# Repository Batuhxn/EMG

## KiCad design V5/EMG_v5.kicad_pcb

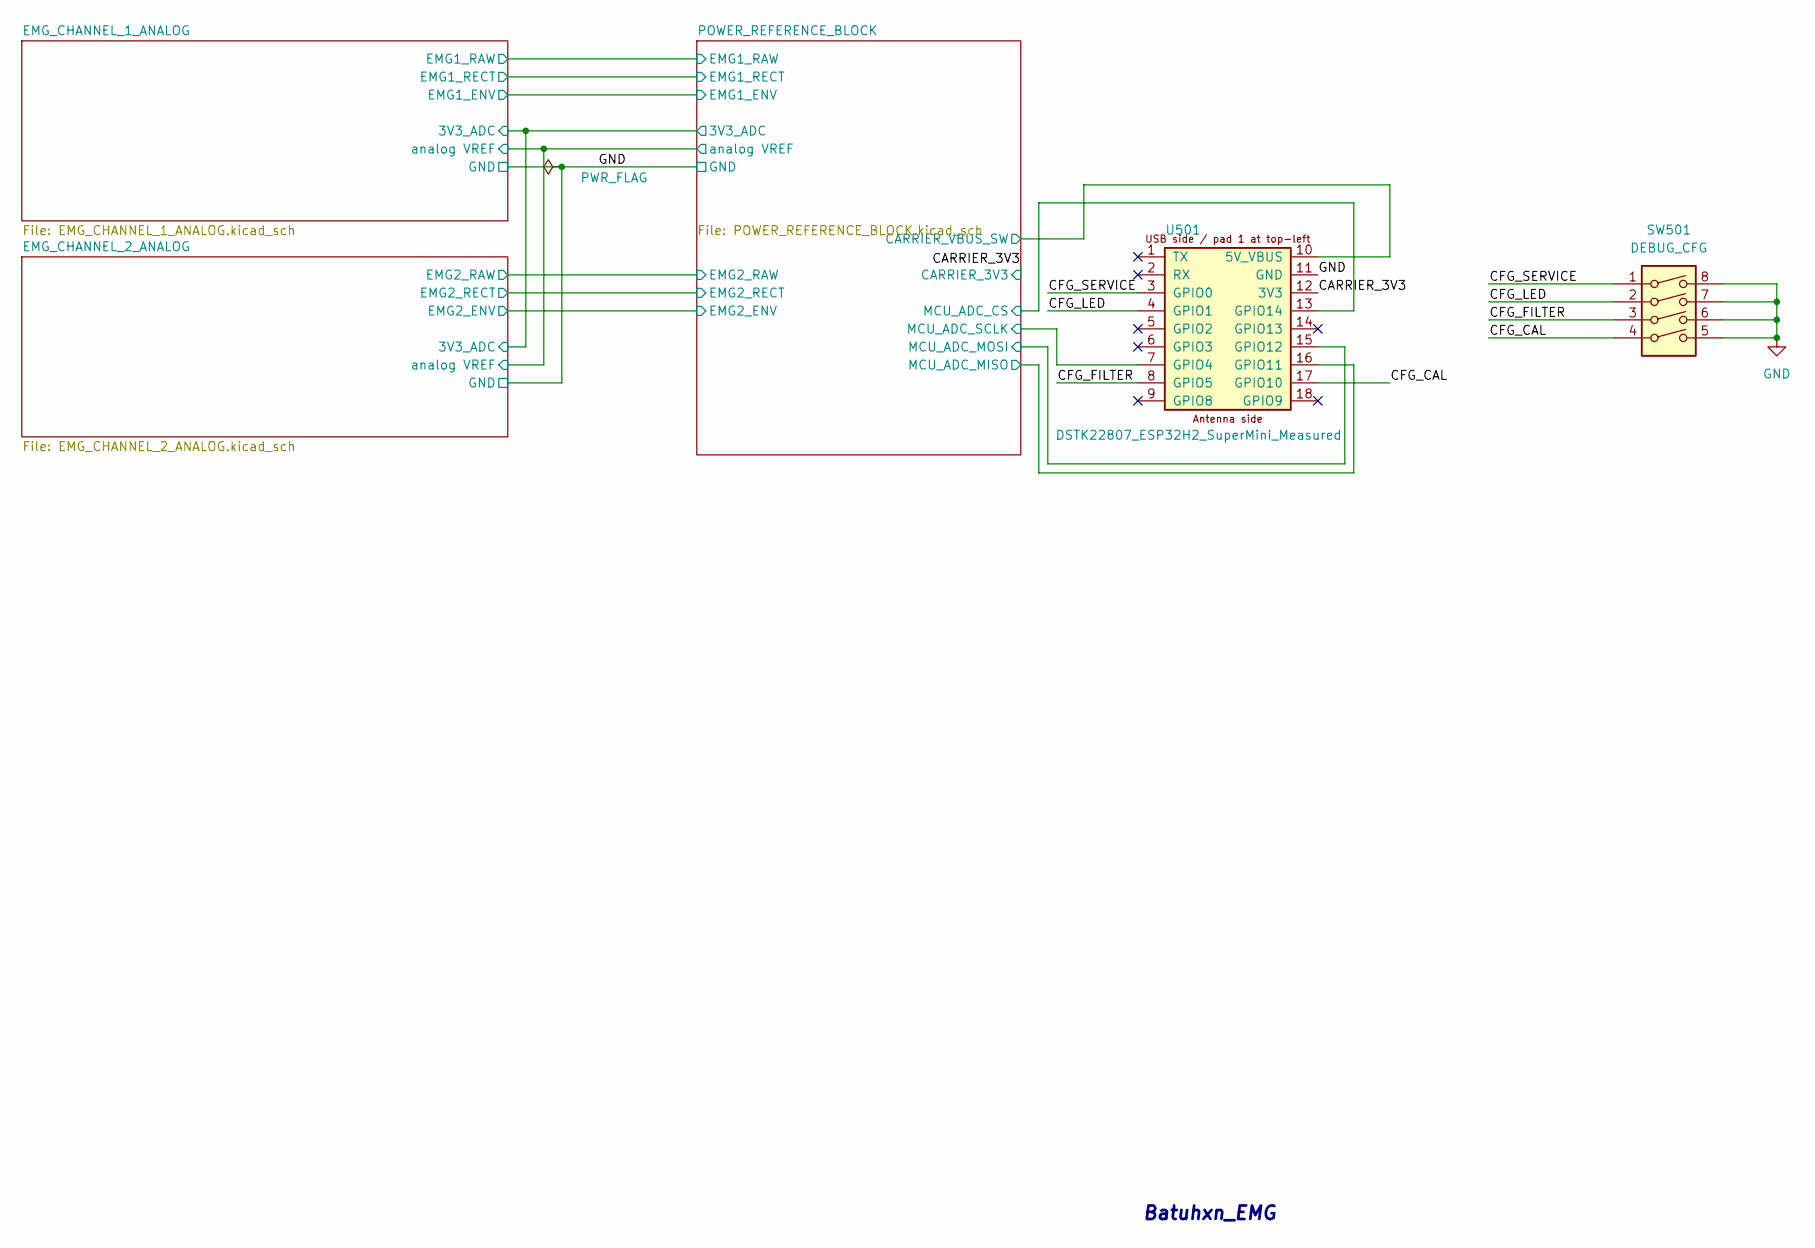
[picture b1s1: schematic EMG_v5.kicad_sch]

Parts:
SW501: DEBUG_CFG; SW_DIP_SPSTx04_Slide_9.78x12.34mm_W7.62mm_P2.54mm
U501: DSTK22807_ESP32H2_SuperMini_Measured; DSTK22807_ESP32H2_SuperMini_Carrier_Measured_THT

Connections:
/CARRIER_3V3: U501.12 (3V3); also elsewhere on the board
/CFG_CAL: SW501.4, U501.17 (GPIO10)
/CFG_FILTER: SW501.3, U501.8 (GPIO5)
/CFG_LED: SW501.2, U501.4 (GPIO1)
/CFG_SERVICE: SW501.1, U501.3 (GPIO0)
/POWER_REFERENCE_BLOCK/CARRIER_VBUS_SW: U501.10 (5V_VBUS); also elsewhere on the board
/POWER_REFERENCE_BLOCK/MCU_ADC_CS: U501.13 (GPIO14); also elsewhere on the board
/POWER_REFERENCE_BLOCK/MCU_ADC_MISO: U501.16 (GPIO11); also elsewhere on the board
/POWER_REFERENCE_BLOCK/MCU_ADC_MOSI: U501.15 (GPIO12); also elsewhere on the board
/POWER_REFERENCE_BLOCK/MCU_ADC_SCLK: U501.7 (GPIO4); also elsewhere on the board
GND: SW501.5, SW501.6, SW501.7, SW501.8, U501.11 (GND); also elsewhere on the board

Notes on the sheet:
Batuhxn_EMG

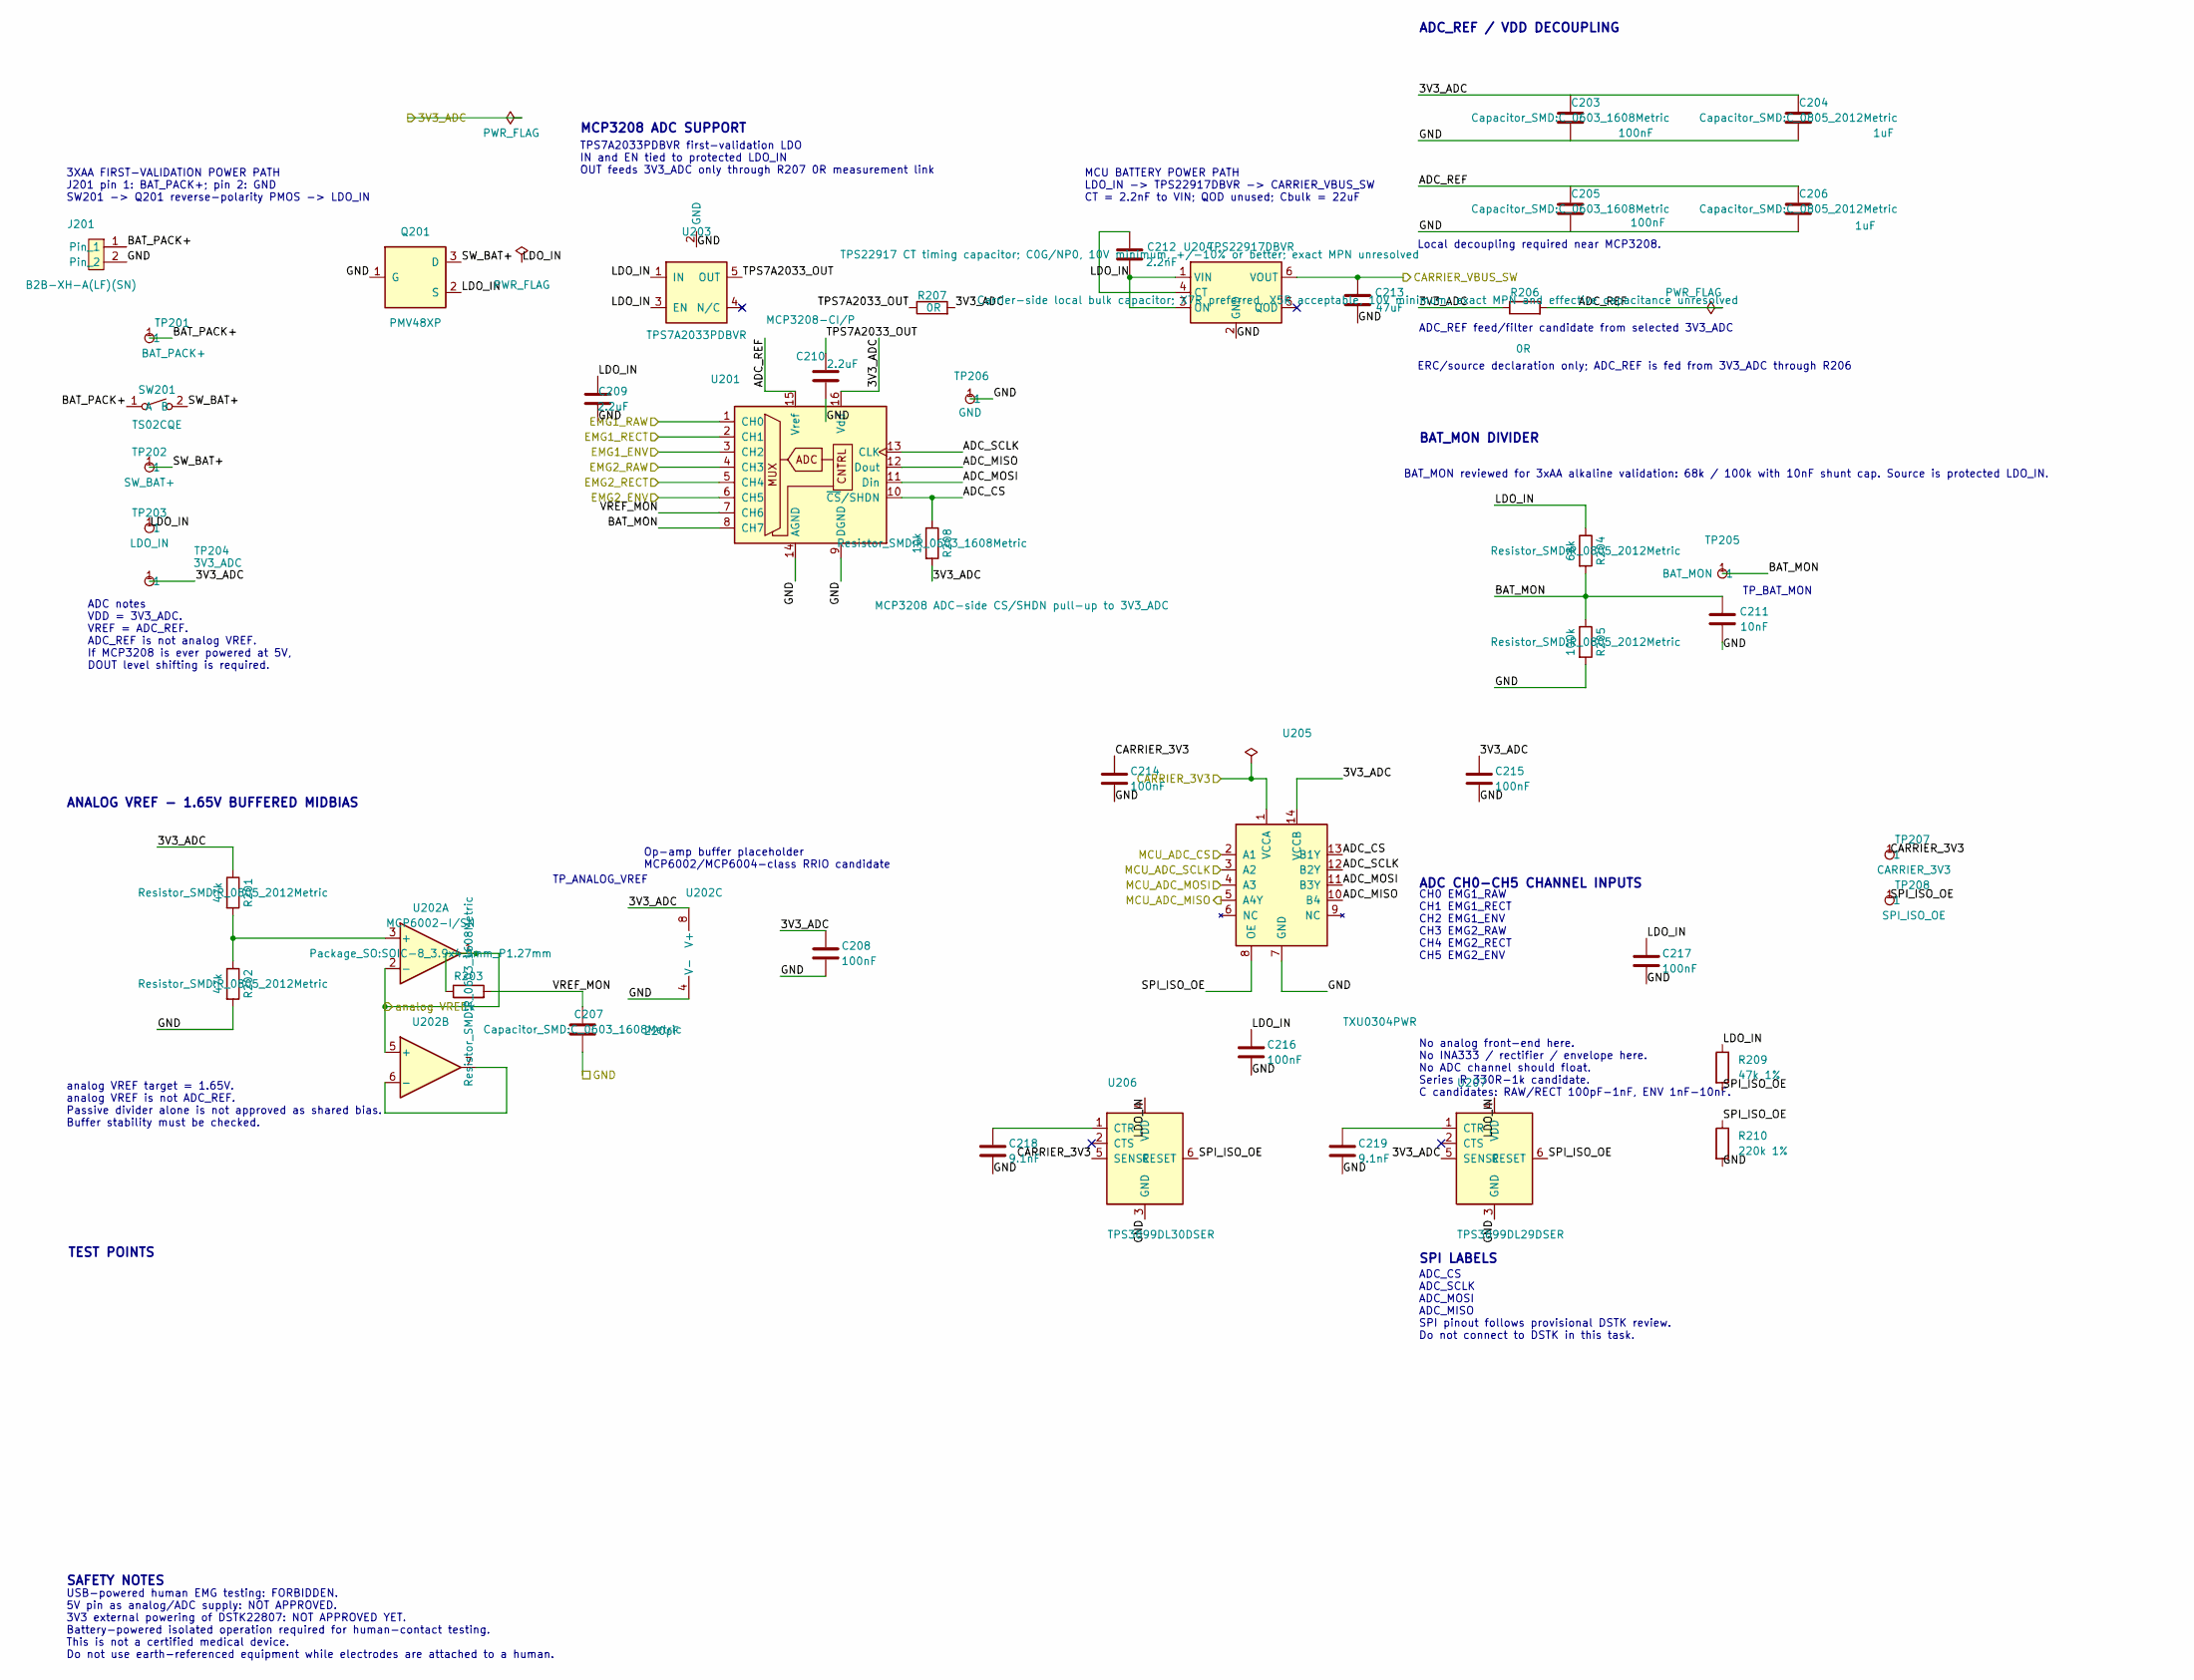
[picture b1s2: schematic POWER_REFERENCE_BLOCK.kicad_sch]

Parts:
C203, C205, C208, C214, C215, C216, C217: 100nF; C_0603_1608Metric
C204, C206: 1uF; C_0805_2012Metric
C207: 220pF; C_0603_1608Metric
C209, C210: 2.2uF; C_0805_2012Metric
C211: 10nF; C_0603_1608Metric
C212: 2.2nF; C_0603_1608Metric
C213: 47uF; C_1210_3225_Murata_GRM32_Reflow
C218, C219: 9.1nF; C_0603_1608Metric
J201: B2B-XH-A(LF)(SN); JST_XH_B2B-XH-A_1x02_P2.50mm_Vertical
Q201: PMV48XP; SOT-23
R201, R202: 47k; R_0805_2012Metric
R203: 1k; R_0603_1608Metric
R204: 68k; R_0805_2012Metric
R205: 100k; R_0805_2012Metric
R206, R207: 0R; R_0603_1608Metric
R208: 10k; R_0603_1608Metric
R209: 47k 1%; R_0603_1608Metric
R210: 220k 1%; R_0603_1608Metric
SW201: TS02CQE; TS02CQE_SPST_THT
TP201: BAT_PACK+; TestPoint_Pad_D1.0mm
TP202: SW_BAT+; TestPoint_Pad_D1.0mm
TP203: LDO_IN; TestPoint_Pad_D1.0mm
TP204: 3V3_ADC; TestPoint_Pad_D1.0mm
TP205: BAT_MON; TestPoint_Pad_D1.0mm
TP206: GND; TestPoint_Pad_D1.0mm
TP207: CARRIER_3V3; TestPoint_Pad_D1.0mm
TP208: SPI_ISO_OE; TestPoint_Pad_D1.0mm
U201: MCP3208-CI/P; DIP-16_W7.62mm
U202: MCP6002-I/SN; SOIC-8_3.9x4.9mm_P1.27mm
U203: TPS7A2033PDBVR; SOT-23-5
U204: TPS22917DBVR; SOT-23-6
U205: TXU0304PWR; TSSOP-14_4.4x5mm_P0.65mm
U206: TPS3899DL30DSER; WSON-6_1.5x1.5mm_P0.5mm
U207: TPS3899DL29DSER; WSON-6_1.5x1.5mm_P0.5mm

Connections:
/CARRIER_3V3: C214.1, TP207.1 (1_1), U205.1 (VCCA), U206.5 (SENSE); also elsewhere on the board
/EMG_CHANNEL_1_ANALOG/3V3_ADC: C203.1, C204.1, C208.1, C215.1, R201.1, R206.1, R207.2, R208.2, TP204.1 (1_1), U201.16 (Vdd), U202.8 (V+), U205.14 (VCCB), U207.5 (SENSE); also elsewhere on the board
/EMG_CHANNEL_1_ANALOG/EMG1_ENV: U201.3 (CH2); also elsewhere on the board
/EMG_CHANNEL_1_ANALOG/EMG1_RAW: U201.1 (CH0); also elsewhere on the board
/EMG_CHANNEL_1_ANALOG/EMG1_RECT: U201.2 (CH1); also elsewhere on the board
/EMG_CHANNEL_1_ANALOG/analog VREF: R203.1, U202.1, U202.2 (-), U202.5 (+); also elsewhere on the board
/EMG_CHANNEL_2_ANALOG/EMG2_ENV: U201.6 (CH5); also elsewhere on the board
/EMG_CHANNEL_2_ANALOG/EMG2_RAW: U201.4 (CH3); also elsewhere on the board
/EMG_CHANNEL_2_ANALOG/EMG2_RECT: U201.5 (CH4); also elsewhere on the board
/POWER_REFERENCE_BLOCK/ADC_CS: R208.1, U201.10 (~CS/SHDN), U205.13 (B1Y)
/POWER_REFERENCE_BLOCK/ADC_MISO: U201.12 (Dout), U205.10 (B4)
/POWER_REFERENCE_BLOCK/ADC_MOSI: U201.11 (Din), U205.11 (B3Y)
/POWER_REFERENCE_BLOCK/ADC_REF: C205.1, C206.1, R206.2, U201.15 (Vref)
/POWER_REFERENCE_BLOCK/ADC_SCLK: U201.13 (CLK), U205.12 (B2Y)
/POWER_REFERENCE_BLOCK/BAT_MON: C211.1, R204.2, R205.1, TP205.1 (1_1), U201.8 (CH7)
/POWER_REFERENCE_BLOCK/BAT_PACK+: J201.1, SW201.1 (A), TP201.1 (1_1)
/POWER_REFERENCE_BLOCK/CARRIER_VBUS_SW: C213.1, U204.6 (VOUT); also elsewhere on the board
/POWER_REFERENCE_BLOCK/LDO_IN: C209.1, C212.2, C216.1, C217.1, Q201.2 (S), R204.1, R209.1, TP203.1 (1_1), U203.1 (IN), U203.3 (EN), U204.1 (VIN), U204.3 (ON), U206.4 (VDD), U207.4 (VDD)
/POWER_REFERENCE_BLOCK/MCU_ADC_CS: U205.2 (A1); also elsewhere on the board
/POWER_REFERENCE_BLOCK/MCU_ADC_MISO: U205.5 (A4Y); also elsewhere on the board
/POWER_REFERENCE_BLOCK/MCU_ADC_MOSI: U205.4 (A3); also elsewhere on the board
/POWER_REFERENCE_BLOCK/MCU_ADC_SCLK: U205.3 (A2); also elsewhere on the board
/POWER_REFERENCE_BLOCK/SPI_ISO_OE: R209.2, R210.1, TP208.1 (1_1), U205.8 (OE), U206.6 (RESET), U207.6 (RESET)
/POWER_REFERENCE_BLOCK/SW_BAT+: Q201.3 (D), SW201.2 (B), TP202.1 (1_1)
/POWER_REFERENCE_BLOCK/TPS7A2033_OUT: C210.1, R207.1, U203.5 (OUT)
/POWER_REFERENCE_BLOCK/VREF_MON: C207.1, R203.2, U201.7 (CH6)
GND: C203.2, C204.2, C205.2, C206.2, C207.2, C208.2, C209.2, C210.2, C211.2, C213.2, C214.2, C215.2, C216.2, C217.2, C218.2, C219.2, J201.2, Q201.1 (G), R202.2, R205.2, R210.2, TP206.1 (1_1), U201.9 (DGND), U201.14 (AGND), U202.4 (V-), U203.2 (GND), U204.2 (GND), U205.7 (GND), U206.3 (GND), U207.3 (GND); also elsewhere on the board
unnamed: R201.2, R202.1, U202.3 (+)
unnamed: U202.6 (-), U202.7
unnamed: C212.1, U204.4 (CT)
unnamed: C218.1, U206.1 (CTR)
unnamed: C219.1, U207.1 (CTR)

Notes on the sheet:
MCP3208 ADC SUPPORT
ADC notes VDD = 3V3_ADC. VREF = ADC_REF. ADC_REF is not analog VREF. If MCP3208 is ever powered at 5V, DOUT level shifting is required.
ADC_REF / VDD DECOUPLING
Local decoupling required near MCP3208.
ANALOG VREF - 1.65V BUFFERED MIDBIAS
analog VREF target = 1.65V. analog VREF is not ADC_REF. Passive divider alone is not approved as shared bias. Buffer stability must be checked.
TP_ANALOG_VREF
Op-amp buffer placeholder MCP6002/MCP6004-class RRIO candidate
BAT_MON DIVIDER
TP_BAT_MON
ADC CH0-CH5 CHANNEL INPUTS
CH0 EMG1_RAW CH1 EMG1_RECT CH2 EMG1_ENV CH3 EMG2_RAW CH4 EMG2_RECT CH5 EMG2_ENV
No analog front-end here. No INA333 / rectifier / envelope here. No ADC channel should float. Series R 330R-1k candidate. C candidates: RAW/RECT 100pF-1nF, ENV 1nF-10nF.
SPI LABELS
ADC_CS ADC_SCLK ADC_MOSI ADC_MISO SPI pinout follows provisional DSTK review. Do not connect to DSTK in this task.
TEST POINTS
SAFETY NOTES
USB-powered human EMG testing: FORBIDDEN. 5V pin as analog/ADC supply: NOT APPROVED. 3V3 external powering of DSTK22807: NOT APPROVED YET. Battery-powered isolated operation required for human-contact testing. This is not a certified medical device. Do not use earth-referenced equipment while elect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
ADC_REF feed/filter candidate from selected 3V3_ADC
ERC/source declaration only; ADC_REF is fed from 3V3_ADC through R206
3XAA FIRST-VALIDATION POWER PATH J201 pin 1: BAT_PACK+; pin 2: GND SW201 -> Q201 reverse-polarity PMOS -> LDO_IN
TPS7A2033PDBVR first-validation LDO IN and EN tied to protected LDO_IN OUT feeds 3V3_ADC only through R207 0R measurement link
BAT_MON reviewed for 3xAA alkaline validation: 68k / 100k with 10nF shunt cap. Source is protected LDO_IN.
MCU BATTERY POWER PATH LDO_IN -> TPS22917DBVR -> CARRIER_VBUS_SW CT = 2.2nF to VIN; QOD unused; Cbulk = 22uF

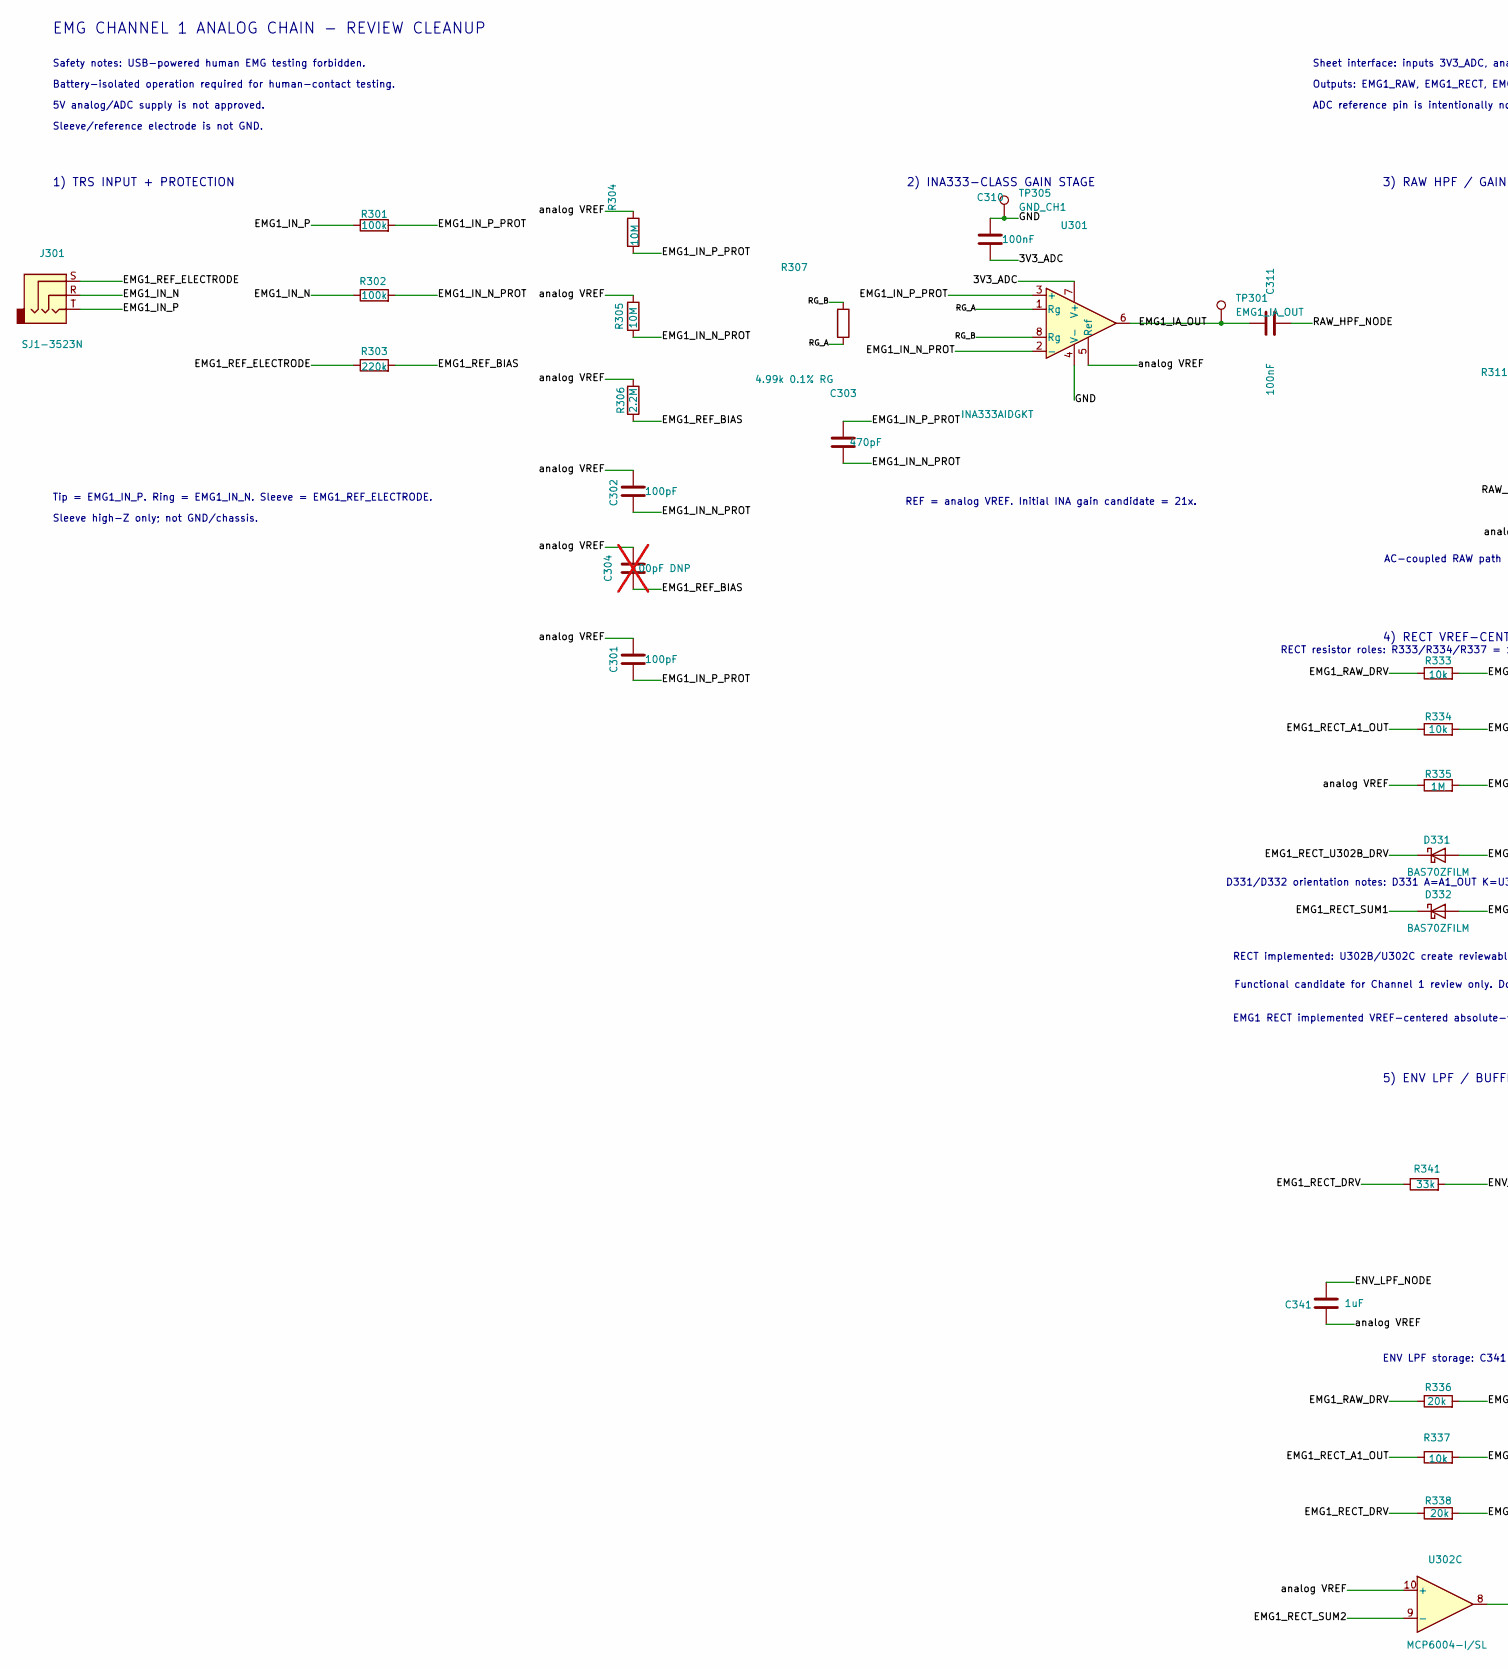
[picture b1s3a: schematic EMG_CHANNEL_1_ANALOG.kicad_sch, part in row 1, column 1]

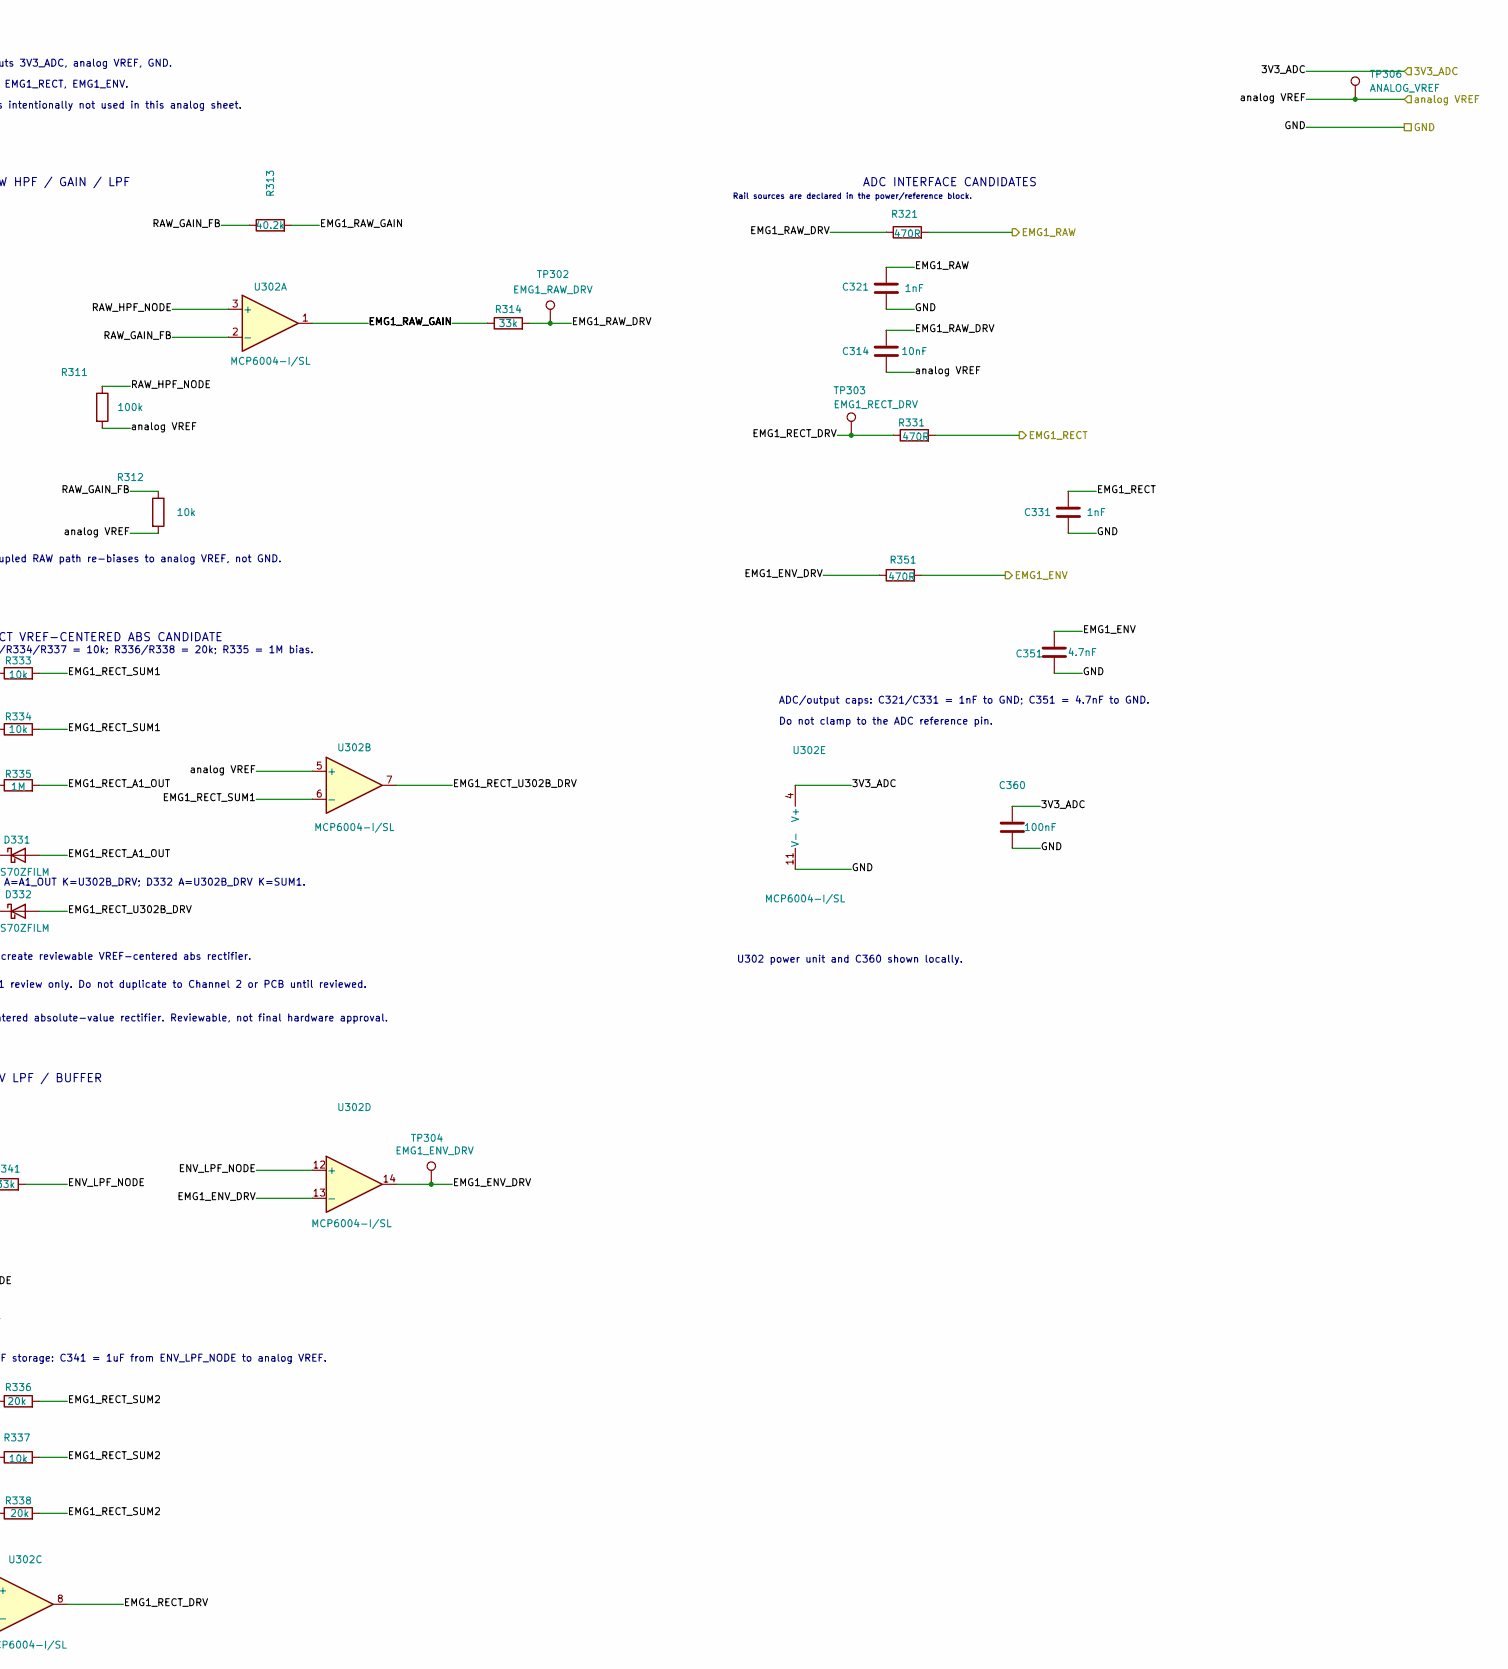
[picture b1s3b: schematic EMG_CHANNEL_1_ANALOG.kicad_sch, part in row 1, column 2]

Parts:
C301, C302: 100pF; C_0603_1608Metric
C303: 470pF; C_0603_1608Metric
C304: 100pF DNP; C_0603_1608Metric; not fitted
C310, C311: 100nF; C_0603_1608Metric
C314: 10nF; C_0603_1608Metric
C321, C331: 1nF; C_0805_2012Metric
C341: 1uF; C_0805_2012Metric
C351: 4.7nF; C_0805_2012Metric
C360: 100nF; C_0805_2012Metric
D331, D332: BAS70ZFILM; D_SOD-123
J301: SJ1-3523N; Jack_3.5mm_CUI_SJ1-3523N_Horizontal
R301, R302: 100k; R_1206_3216Metric
R303: 220k; R_1206_3216Metric
R304, R305: 10M; R_1206_3216Metric
R306: 2.2M; R_1206_3216Metric
R307: 4.99k 0.1% RG; R_0805_2012Metric
R311: 100k; R_0805_2012Metric
R312, R333, R334, R337: 10k; R_0805_2012Metric
R313: 40.2k; R_0805_2012Metric
R314, R341: 33k; R_0805_2012Metric
R321, R331, R351: 470R; R_0805_2012Metric
R335: 1M; R_0805_2012Metric
R336, R338: 20k; R_0805_2012Metric
TP301: EMG1_IA_OUT; TestPoint_Pad_D1.5mm
TP302: EMG1_RAW_DRV; TestPoint_Pad_D1.5mm
TP303: EMG1_RECT_DRV; TestPoint_Pad_D1.5mm
TP304: EMG1_ENV_DRV; TestPoint_Pad_D1.5mm
TP305: GND_CH1; TestPoint_Pad_D2.0mm
TP306: ANALOG_VREF; TestPoint_Pad_D1.5mm
U301: INA333AIDGKT; INA333_DGK_VSSOP-8_TI
U302: MCP6004-I/SL; SOIC-14_3.9x8.7mm_P1.27mm

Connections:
/EMG_CHANNEL_1_ANALOG/3V3_ADC: C310.2, C360.1, U301.7 (V+), U302.4 (V+); also elsewhere on the board
/EMG_CHANNEL_1_ANALOG/EMG1_ENV: C351.1, R351.2; also elsewhere on the board
/EMG_CHANNEL_1_ANALOG/EMG1_ENV_DRV: R351.1, TP304.1 (1_1), U302.13 (-), U302.14
/EMG_CHANNEL_1_ANALOG/EMG1_IA_OUT: C311.1, TP301.1 (1_1), U301.6
/EMG_CHANNEL_1_ANALOG/EMG1_IN_N: J301.R, R302.1
/EMG_CHANNEL_1_ANALOG/EMG1_IN_N_PROT: C302.2, C303.2, R302.2, R305.2, U301.2 (-)
/EMG_CHANNEL_1_ANALOG/EMG1_IN_P: J301.T, R301.1
/EMG_CHANNEL_1_ANALOG/EMG1_IN_P_PROT: C301.2, C303.1, R301.2, R304.2, U301.3 (+)
/EMG_CHANNEL_1_ANALOG/EMG1_RAW: C321.1, R321.2; also elsewhere on the board
/EMG_CHANNEL_1_ANALOG/EMG1_RAW_DRV: C314.1, R314.2, R321.1, R333.1, R336.1, TP302.1 (1_1)
/EMG_CHANNEL_1_ANALOG/EMG1_RAW_GAIN: R313.2, R314.1, U302.1
/EMG_CHANNEL_1_ANALOG/EMG1_RECT: C331.1, R331.2; also elsewhere on the board
/EMG_CHANNEL_1_ANALOG/EMG1_RECT_A1_OUT: D331.2 (A), R334.1, R335.2, R337.1
/EMG_CHANNEL_1_ANALOG/EMG1_RECT_DRV: R331.1, R338.1, R341.1, TP303.1 (1_1), U302.8
/EMG_CHANNEL_1_ANALOG/EMG1_RECT_SUM1: D332.1 (K), R333.2, R334.2, U302.6 (-)
/EMG_CHANNEL_1_ANALOG/EMG1_RECT_SUM2: R336.2, R337.2, R338.2, U302.9 (-)
/EMG_CHANNEL_1_ANALOG/EMG1_RECT_U302B_DRV: D331.1 (K), D332.2 (A), U302.7
/EMG_CHANNEL_1_ANALOG/EMG1_REF_BIAS: C304.2, R303.2, R306.2
/EMG_CHANNEL_1_ANALOG/EMG1_REF_ELECTRODE: J301.S, R303.1
/EMG_CHANNEL_1_ANALOG/ENV_LPF_NODE: C341.1, R341.2, U302.12 (+)
/EMG_CHANNEL_1_ANALOG/RAW_GAIN_FB: R312.1, R313.1, U302.2 (-)
/EMG_CHANNEL_1_ANALOG/RAW_HPF_NODE: C311.2, R311.1, U302.3 (+)
/EMG_CHANNEL_1_ANALOG/RG_A: R307.2, U301.1 (Rg)
/EMG_CHANNEL_1_ANALOG/RG_B: R307.1, U301.8 (Rg)
/EMG_CHANNEL_1_ANALOG/analog VREF: C301.1, C302.1, C304.1, C314.2, C341.2, R304.1, R305.1, R306.1, R311.2, R312.2, R335.1, TP306.1 (1_1), U301.5 (Ref), U302.5 (+), U302.10 (+); also elsewhere on the board
GND: C310.1, C321.2, C331.2, C351.2, C360.2, TP305.1 (1_1), U301.4 (V-), U302.11 (V-); also elsewhere on the board

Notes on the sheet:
EMG CHANNEL 1 ANALOG CHAIN - REVIEW CLEANUP
Safety notes: USB-powered human EMG testing forbidden.
Battery-isolated operation required for human-contact testing.
5V analog/ADC supply is not approved.
Sleeve/reference electrode is not GND.
Sheet interface: inputs 3V3_ADC, analog VREF, GND.
Outputs: EMG1_RAW, EMG1_RECT, EMG1_ENV.
ADC reference pin is intentionally not used in this analog sheet.
Rail sources are declared in the power/reference block.
1) TRS INPUT + PROTECTION
Tip = EMG1_IN_P. Ring = EMG1_IN_N. Sleeve = EMG1_REF_ELECTRODE.
Sleeve high-Z only; not GND/chassis.
2) INA333-CLASS GAIN STAGE
REF = analog VREF. Initial INA gain candidate = 21x.
3) RAW HPF / GAIN / LPF
AC-coupled RAW path re-biases to analog VREF, not GND.
4) RECT VREF-CENTERED ABS CANDIDATE
RECT implemented: U302B/U302C create reviewable VREF-centered abs rectifier.
Functional candidate for Channel 1 review only. Do not duplicate to Channel 2 or PCB until reviewed.
5) ENV LPF / BUFFER
ENV LPF storage: C341 = 1uF from ENV_LPF_NODE to analog VREF.
U302 power unit and C360 shown locally.
ADC INTERFACE CANDIDATES
ADC/output caps: C321/C331 = 1nF to GND; C351 = 4.7nF to GND.
Do not clamp to the ADC reference pin.
D331/D332 orientation notes: D331 A=A1_OUT K=U302B_DRV; D332 A=U302B_DRV K=SUM1.
RECT resistor roles: R333/R334/R337 = 10k; R336/R338 = 20k; R335 = 1M bias.
EMG1 RECT implemented VREF-centered absolute-value rectifier. Reviewable, not final hardware approval.
